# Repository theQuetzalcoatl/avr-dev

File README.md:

# avr-dev

A self made and designed embedded development board with several peripherals/devices to use. On top of that is an embedded kernel with several device drivers, forming an OS.</br>
The project aims to develop a suitable SW architecture and a corresponding HW development board, which can be the foundation of learning and experimentation.

### [Hardware](https://github.com/theQuetzalcoatl/avr-dev/blob/master/HW/README.md "Hardware"):

* LCD
* DAC
* Buzzer
* LEDs & buttons
* Keypad
* UART (potentially USB)
* Temperature sensing
* Light sensing
* Capacitive touch sensing
* Voltage/angle sensing
* Rotary encoder

### [Software](https://github.com/theQuetzalcoatl/avr-dev/blob/master/SW/Application/README.md "Software"):

* A primitive, embedded OS
* Device drivers for HAL
* Application

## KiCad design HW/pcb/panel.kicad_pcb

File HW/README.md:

# Hardware

This file is intended to keep track and present the more detailed informations about the HW part of the project.
The PCB is currently developed in KiCAD. 
---
### HW elements:
* **DAC**: A first order RC low pass filter with variing duty cycle PWM on its input
* **LCD**: A 2x16 display. Backlight can be switched on/off by SW
* **Buzzer**: MOSFET switched, frequency can be set by SW
* **LEDS & buttons**: 4 leds, two push buttons without external pullup resistors
* **Keypad**: a simple 3 by 4 one</br>
      |1|2|3|</br>
      |4|5|6|</br>
      |7|8|9|</br>
      |*|0|#|</br>
* **UART**: Jumper pins for UART  communication, with a suitable connector USB is possible using the CH340G based USB/UART module
* **Temp sensing**: A PT1000 and a current source is used
* **Light sensing**: An LDR is used alongside a regular pot. meter so treshold can also be set
* **Capacitive touch sensing**: Two buttons are made with using only one GPIO each
* **Voltage/angle sensing**: A regular pot meter will supply the devided Vcc voltage. It can be turned and as such, can be used as an angle sensor
* **Rotary encoder**: Capacitors are placed on the MCU pins to help with debouncing

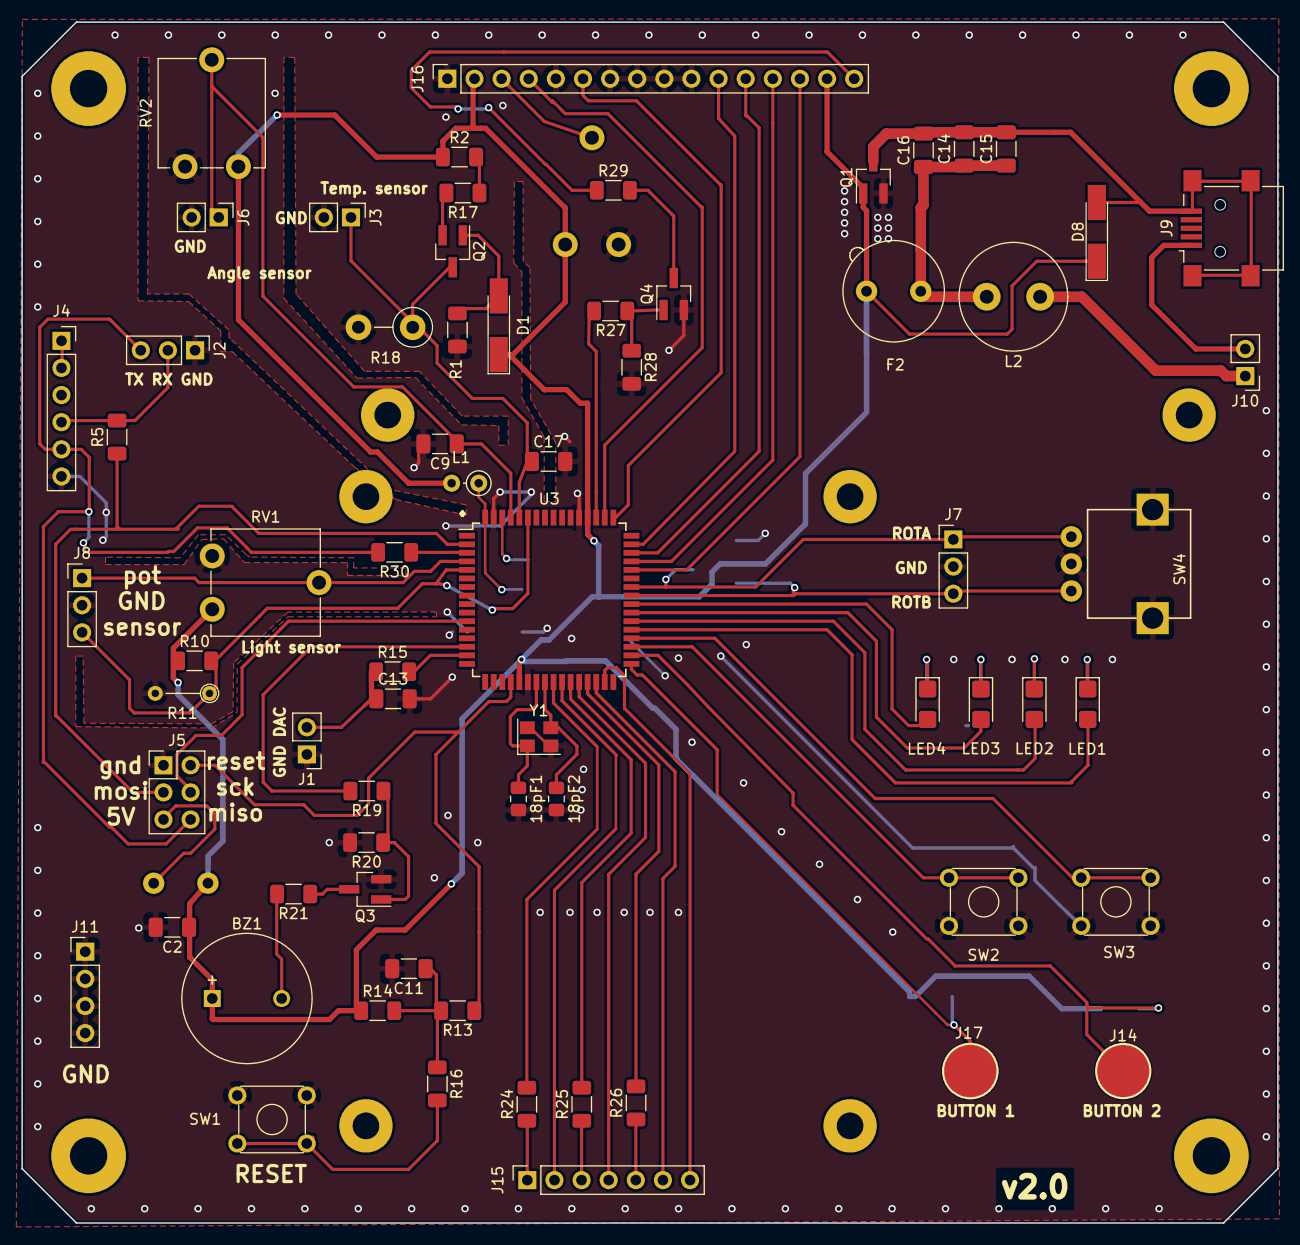
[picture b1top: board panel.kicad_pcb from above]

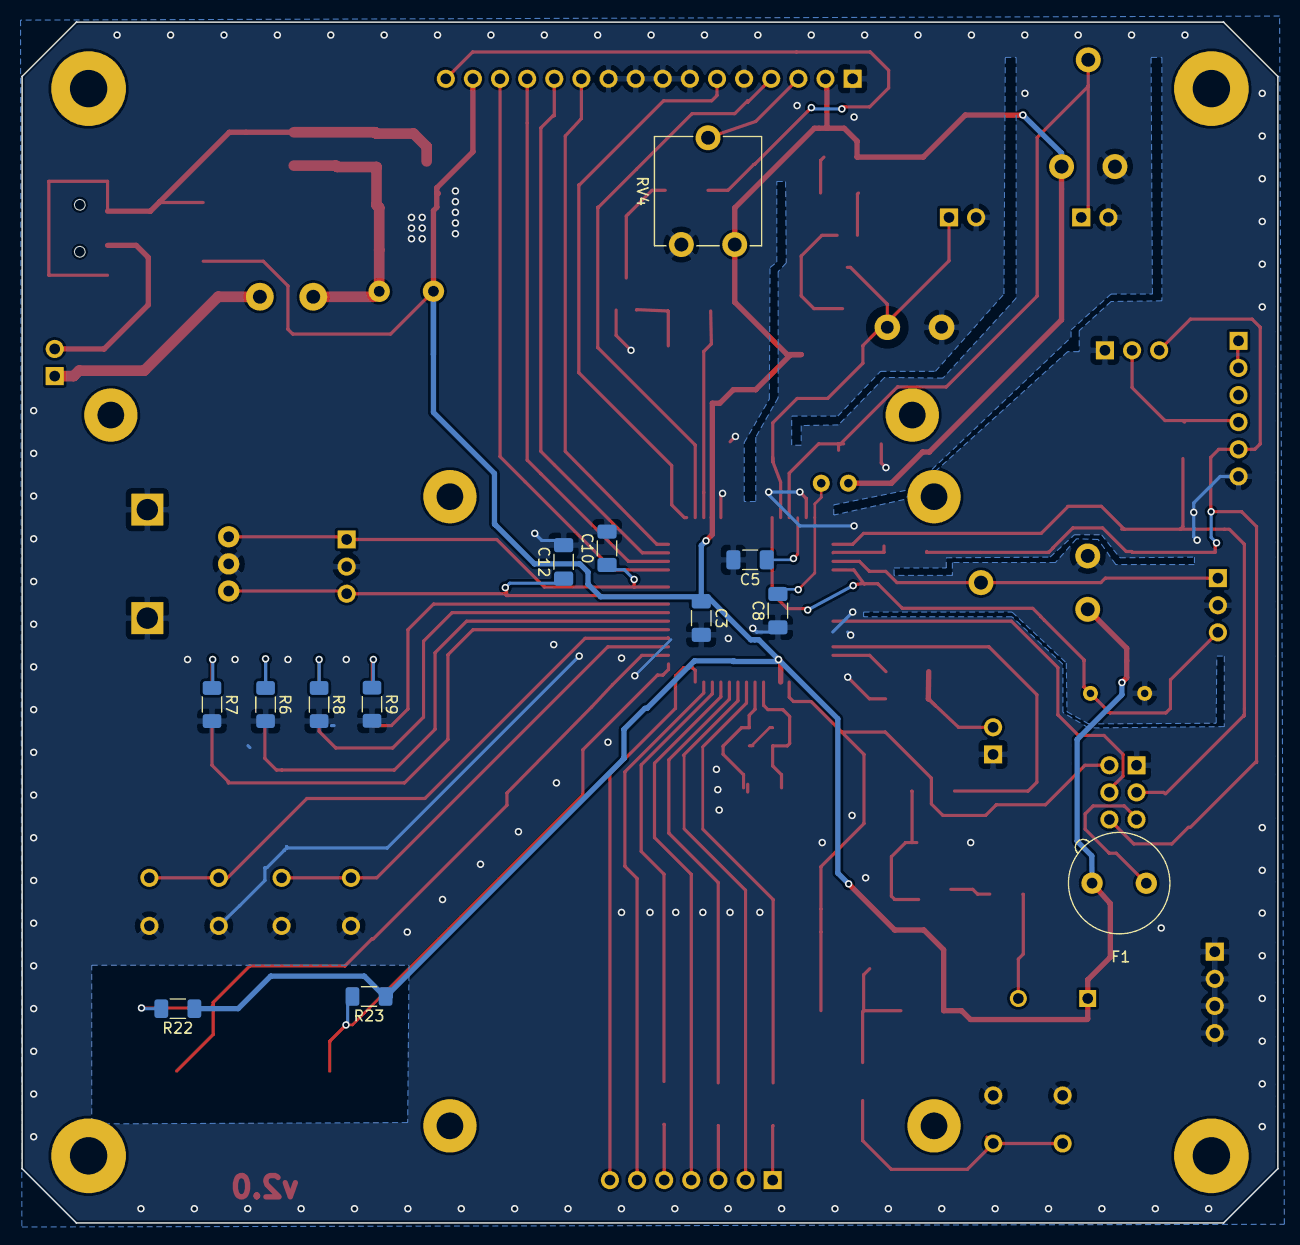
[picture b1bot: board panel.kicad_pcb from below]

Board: 2 copper layers, 117.6 x 112.5 mm, 91 parts (13 on the bottom side), 68 nets.

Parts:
18pF1, 18pF2: 18pF; C_0805_2012Metric_Pad1.18x1.45mm_HandSolder
BZ1: Buzzer; MagneticBuzzer_ProSignal_ABT-410-RC
C2, C5, C9, C16: 100nF; C_1206_3216Metric_Pad1.33x1.80mm_HandSolder
C3: C; C_1206_3216Metric_Pad1.33x1.80mm_HandSolder
C8: 100n; C_1206_3216Metric_Pad1.33x1.80mm_HandSolder
C10, C11, C12, C15, C17: 10nF; C_1206_3216Metric_Pad1.33x1.80mm_HandSolder
C13: 150nF; C_1206_3216Metric_Pad1.33x1.80mm_HandSolder
C14: 1nF; C_1206_3216Metric_Pad1.33x1.80mm_HandSolder
D1: 3_6BreakDown; D_MiniMELF_Handsoldering
D8: 5VBreakdown_Zener; D_MiniMELF_Handsoldering
F1, F2: Fuse_Small; Fuseholder_Fuse_TR5_Littlefuse-No560_No460
J1, J6: Conn_01x02_Male; PinHeader_1x02_P2.54mm_Vertical
J2: USART test points; PinHeader_1x03_P2.54mm_Vertical
J3: Conn_01x02_Male; Pin_Header_Straight_1x02_Pitch2.54mm
J4: uart_conn; PinSocket_1x06_P2.54mm_Vertical
J5: Conn_02x03_Odd_Even; PinHeader_2x03_P2.54mm_Vertical
J7, J8: Conn_01x03_Male; PinHeader_1x03_P2.54mm_Vertical
J9: USB_B_Mini; USB_Mini-B_Lumberg_2486_01_Horizontal
J10: current sense; PinHeader_1x02_P2.54mm_Vertical
J11: GND conn; PinHeader_1x04_P2.54mm_Vertical
J14, J17: TEST_1P; Measurement_Point_Round-SMD-Pad_Big
J15: Conn_01x07_Female; PinSocket_1x07_P2.54mm_Vertical
J16: Conn_01x16; PinSocket_1x16_P2.54mm_Vertical
J19, J23, J28, J29, J30, J31: Conn_01x01; MountingHole_2.5mm_Pad
J24, J25, J26, J27: Conn_01x01; MountingHole_3.5mm_Pad
L1: Ferrite_Bead; L_Axial_L5.3mm_D2.2mm_P2.54mm_Vertical_Vishay_IM-1
L2: L_Core_Ferrite; L_Radial_D10.0mm_P5.00mm_Fastron_07M
LED1, LED2, LED3, LED4: blue; LED_1206_3216Metric_Castellated
Q1, Q3, Q4: Q_NMOS_GSD; SOT-23_Handsoldering
Q2: BC807; SOT-23_Handsoldering
R1, R6, R7, R8, R9: 270; R_1206_3216Metric_Pad1.30x1.75mm_HandSolder
R2: 200; R_1206_3216Metric_Pad1.30x1.75mm_HandSolder
R5, R19, R21, R30: 12; R_1206_3216Metric_Pad1.30x1.75mm_HandSolder
R10: 200k; R_1206_3216Metric_Pad1.30x1.75mm_HandSolder
R11: LDR; R_Axial_DIN0204_L3.6mm_D1.6mm_P5.08mm_Vertical
R13: 470; R_1206_3216Metric_Pad1.30x1.75mm_HandSolder
R14, R15: 10k; R_1206_3216Metric_Pad1.30x1.75mm_HandSolder
R16, R27: 100; R_1206_3216Metric_Pad1.30x1.75mm_HandSolder
R17: 2k7; R_1206_3216Metric_Pad1.30x1.75mm_HandSolder
R18: PT1000; R_Axial_DIN0411_L9.9mm_D3.6mm_P5.08mm_Vertical
R20, R28: 100k; R_1206_3216Metric_Pad1.30x1.75mm_HandSolder
R22, R23: 470k; R_1206_3216Metric_Pad1.30x1.75mm_HandSolder
R24, R25, R26: 2.2k; R_1206_3216Metric_Pad1.30x1.75mm_HandSolder
R29: 91; R_1206_3216Metric_Pad1.30x1.75mm_HandSolder
RV1, RV2, RV4: 10k; Potentiometer_ACP_CA9-V10_Vertical
SW1, SW2, SW3: SW_Push_Dual_OWN; SW_TH_Tactile_Omron_B3F-10xx
SW4: Rotary_Encoder_With_CaseHolder; Rotary_Encoder_CaseHolder
U3: ATMEGA128-16AU; TQFP-64_14x14mm_P0.8mm
Y1: Crystal_GND24_Small; Crystal_SMD_3225-4Pin_3.2x2.5mm

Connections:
+5V: BZ1.1, C2.1, C3.1, D1.1, D8.1, F1.2, F2.2, J16.2, J16.15, L1.2, Q1.1, R2.1, R10.1, R14.1, R22.1, R23.1, RV1.1, RV2.1, RV4.1, U3.21, U3.52
/Input_filter/DC_1: J9.1, J10.2
/Input_filter/DC_2: C14.2, C15.2, C16.2, D8.2, J9.5, J9.6, Q1.3
/Keypad/col_1: R25.2, U3.27
/Keypad/col_2: R24.2, U3.25
/Keypad/col_3: R26.2, U3.29
/Keypad/row_1: J15.2, U3.26
/Keypad/row_2: J15.7, U3.31
/Keypad/row_3: J15.6, U3.30
/Keypad/row_4: J15.4, U3.28
/LCD_/Backlight: R27.2, U3.51
/LCD_/D4: J16.11, U3.47
/LCD_/D5: J16.12, U3.46
/LCD_/D6: J16.13, U3.45
/LCD_/D7: J16.14, U3.44
/LCD_/EN: J16.6, U3.49
/LCD_/RS: J16.4, U3.50
BUTT1: SW2.1, SW2.2, U3.35
BUTT2: SW3.1, SW3.2, U3.36
Buzzer: R19.2, U3.14
Capacitive_button_1: J17.1, R23.2, U3.33
Capacitive_button_2: J14.1, R22.2, U3.34
DAC: R15.2, U3.15
GNDREF: 18pF1.2, 18pF2.2, C2.2, C3.2, C5.2, C8.1, C9.2, C10.2, C11.2, C12.2, C13.2, C17.2, J1.1, J2.1, J3.2, J4.6, J5.1, J6.2, J7.2, J8.2, J11.1, J11.2, J11.3, J11.4, J16.1, J16.5, J16.7, J16.8, J16.9, J16.10, Q1.2, Q3.2, Q4.2, R1.2, R6.2, R7.2, R8.2, R9.2, R11.2, R18.2, R20.2, R28.2, RV1.3, RV2.3, RV4.3, SW1.1, SW1.2, SW2.3, SW2.4, SW3.3, SW3.4, SW4.2, SW4.4, SW4.5, U3.22, U3.53, U3.63, Y1.2, Y1.4
LDR_divider: J8.3, R10.2, R11.1, U3.5, U3.59
LED1: LED1.2, U3.37
LED2: LED2.2, U3.38
LED3: LED3.2, U3.39
LED4: LED4.2, U3.40
MISO: J2.3, J4.5, J5.6, R30.2
MOSI: J5.3, R5.1, U3.2
unnamed: 18pF1.1, U3.23, Y1.1
unnamed: 18pF2.1, U3.24, Y1.3
unnamed: BZ1.2, R21.2
unnamed: C5.1, U3.62
unnamed: C8.2, L1.1, U3.64
unnamed: C11.1, R13.2, R14.2, R16.1
unnamed: C13.1, J1.2, R15.1
unnamed: C14.1, C15.1, C16.1, F2.1, L2.2
unnamed: D1.2, Q2.1, R1.1
unnamed: F1.1, J5.5
unnamed: J2.2, J4.4, R5.2
unnamed: J4.1, J4.2
unnamed: J10.1, L2.1
unnamed: J15.1, R24.1
unnamed: J15.3, R25.1
unnamed: J15.5, R26.1
unnamed: J16.3, RV4.2
unnamed: J16.16, R29.1
unnamed: LED1.1, R7.1
unnamed: LED2.1, R6.1
unnamed: LED3.1, R8.1
unnamed: LED4.1, R9.1
unnamed: Q2.2, R17.2
unnamed: Q3.1, R19.1, R20.1
unnamed: Q3.3, R21.1
unnamed: Q4.1, R27.1, R28.1
unnamed: Q4.3, R29.2
unnamed: R16.2, SW1.3, SW1.4
unnamed: R2.2, R17.1
unnamed: R30.1, U3.3
Pot.meter: J8.1, RV1.2, U3.4
RESET_MEGA: J5.2, R13.1, U3.20
ROTA: C10.1, J7.1, SW4.1, U3.42
ROTB: C12.1, J7.3, SW4.3, U3.41
SCK: J5.4, U3.11
Temperature: C17.1, J3.1, Q2.3, R18.1, U3.60
Voltage_sensor: C9.1, J6.1, RV2.2, U3.61

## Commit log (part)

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2020-03-21 Created and added some content to GITIGNORE.
2020-04-25 Created main Makefile and defined the basic structure of it.
2020-04-26 - Added source code discovering section - Added 'upload' target that will be able to being run
2020-04-26 - Made 'upload' target in main Makefile a phony - Updated Component folder structure to include 'model' folder - Created HSI.h header file which will contain important information about the HW.
2020-04-26 - Created folder structure of OS component, also created several source files
2020-05-02 Updated README.
2020-05-02 - Added HW/readme with some content - Updated System readme, corrected ADC->DAC - Updated some comments is SW Makefile - Added SW readme with some content
2020-05-06 HSI update - Supply voltage - IO treshold values
2020-05-06 Added macros to math.h
2020-05-16 Made TODO list look a little bit nicer
2020-09-04 More points added after examining the v1.0 board
2020-09-28 Updated HW TODOs for V2.0
2020-09-28 - Moved the main Application's content into a new folder - created 'examples' section with, well..examples.
2020-10-04 Corrected PORTB to LCD_PORT during the initialization.
2020-10-07 * Created new, rotary encoder example source code * Modified the license statements at the end of some files
2020-10-29 * corrected GPL in some files * created new example code for the light sensor
2020-11-29 Created new example code for the potmeter ADC.
2020-12-21 New example for the keyboard.
2020-12-24 Created example fir capacitive touch buttons.
2021-01-04 * Removed Makefile because it was unnecessary. Added a bash script in its stead. * Updated README
2021-01-04 Added the gerber files.
2021-05-25 * pictures weren't really changed
2021-05-25 * License and gitignore weren't changed.
2021-05-25 * files were deleted because of folder structure change
2021-05-25 * Renamed for a clearer purpose.
2021-05-25 * updated the examples to fit to the board 2.0v. * added temperature sensing example. * added fuse bit setting for 16 MHz external asc. and ATmega103 compatibility mode disabling
2021-05-30 * The picture was cropped due to image size limitations. Collage is out, trying to upload them individually.
2021-05-30 * Even lower res was created.
2021-05-30 * For some reason, Github differentiated between the same sized pictures, so the full ones were further reduced to 800 width.
2021-07-28 Added bullet points to TODO list for version 3 of the board.
2021-07-28 moved schematic pdf under schematic/
2021-07-28 I don't know exactly what has changed.
2021-07-29 Some of the device drivers were partially implemented
2021-07-29 Created a preemtive kernel with Round Robin scheduling algorithm
2021-07-30 Created a build script. * deletes all object files * compiles all source files * info about size * with an "upload" argument it burns the code to the target
2021-07-30 * Removed current thread pointer - was not being used * removed 'id' from Thread struct, because it was not needed anywhere in the kernel
2021-07-30 Corrected some comments.
2021-07-31 Replaced C stack pointer storing instruction with less, faster assembly instructions. Now context switching is faster.
2021-08-03 * Moved macros from kernel header to c file because currently they are only used in that module * Started adding guide comments to kernel APIs * By reseting TIMER0 at the end of every context restora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
2021-08-05 * decapitalized the drivers folder
2021-08-05 * Changed including of drivers to be lowercase
2021-08-06 * Changed a thread's address' type from snake case to camel case to be consistent with the other ones. * Decremented the minimum stack requirement because it still included RAMPZ register.
2021-08-06 * separated kernel error handling from the main code * kernel error code now prepended by a K * all future error handling shall take place in the error handling files
    * Corrected some error codes
    * Introduced new variable to TCB - num of active threads.
    * is reduced when a thread is halted.
    * will be used when a proper delaying mechanism will be implemented.
    * system now gently halts when the last one of the threads is being deleted.
    * implemented thread number checking
2021-08-09 * Applied cast to operation in order to reduce generated assembly instruction by 2. (Not much, ut it's honest work)
2021-08-09 * Added functionality get a button press. * Created button codes.
2021-08-09 * Moved ATOMIC operation to kernel header in order for the drivers to use. * Did not put 'extern void disable_systick(void)' into kernel header because it should only be reachable by the kernel and i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
2021-08-09 * Created lcd driver with basic functionalities.
2021-08-10 * Removed waiting ticks field form Thread struct because it has no use yet.
2021-08-11 * Got system tick init closer to start of the function because if we shouldn't initialize the drivers if we could not init the systick * Fixed returning error code from init_system_ticking, as it is 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
2021-08-11 * char get_pressed_key --> keypad_get_pressed_key to be clear that that it is the keypad driver's API
2021-08-12 * Changed the kernel to use Timer 2 to generate the systick instead of Timer 0 because the Buzzer will use Timer 0 to generate sound. * Also changed the scaling of the systick based in microseconds i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
2021-08-15 * Properly made init function of the buzzer, which is mostly its timer's initialization * Added device functionalities * buzzing at a certain (unaccurate) frequency * safely stopping the buzzer
2021-08-18 * Modified build script so that it does not burn the uC when compilation fails.
2021-08-19 * Wrote notifying comments about the placement of fields in Thread and TCB data structures. * Corrected max MS tick's justification comment, prescaler was still the old value. * Made the task switch 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
2021-08-19 * Introduced restrictions on the microcontroller frequency. For now, only 8 and 16MHz is allowed. * Introduced minimum systick , and it shall be 100 us. Because now a context switch is about 15 us. *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
2021-08-20 * Some of the configuration macros got CONFIG_ prefix to emphasize that they are changeable configurations
2021-08-23 * Added MindMap file to be ignored.
2021-08-24 * modified, added some comments for better understanding * Added const qualifiers where they were needed * Rearranged the function in kernel.c and created a SYSCALL section for more logical understan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
2021-08-24 * thread state definitions were moved to header, so the application code can use it when getting another thread's state * 'turn_led_on' and 'turn_led_off' functions got atomic write because of a bug 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
2021-08-28 * Added GPLv2 license to all the source files
2021-08-29 * Introduced the first script * it does as the name implies * tested it on the system, cought the first problem, so error_handling was renamed wo kernel_error_handling. * if I changed the header guar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
2021-08-29 * header guard script now have start-end section for better readability in the log stream. Also if it finds at least one wrong header file, it will exit with 1, enabling the build system to halt if n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
2021-09-09 * Introduced kernel version for the application/driver layer which will be the latest tag number.
2021-09-23 * changed the types from capital initiale to <type>_t because i think it is better this way.
2021-09-24 * moved a function, added some explanation to a syscall
2021-09-25 * started reforming the error handling system * introduced error type * maximum of 128 errors can be recognised by the kernel, with the MSB set to 1 * implemented stack registering checking. Now the 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
2021-10-12 * Changed driver system * Short: Now new function pair will be implemented(lease, release) which are analogous to 'open' and 'close'. The caller gets a device ID, and with it, can call certain functi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
2021-10-12 * Updated main and utils to reflect the changes made to the driver system
2021-10-16 * Introduced (re)leasing driver system to LCD. * applied atomic areas when leasing to make it safer, less concurrent. * created LCD driver ID in kernel
2021-10-16 * Added LCD driver ID
2021-10-16 * Updated the user application according to the changes
2021-10-19 * removed lease - release pair, as it is handled by the kernel. * now in critical functions, checking for ownership of the device * implemented internal command sending to simplfiy the initialization.
2021-10-19 * Uptaed example application code
2021-10-22 * Created a new lcd function 'lcd_print' to print strings. * created an internalwrite as well to be faster. * Also found a bug, at startup, if the first thread is run, and runs to exit before a conte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
2021-10-22 * Updated example application.
2021-10-23 * Made it so now if a thread does not release a device before it exits, the kernel we do so on its behalf. * Updated application example
2021-10-30 * registered UART amongs the devices in the kernel
2021-10-30 * Updated example application according to changes made
2021-10-31 * separated the OS code from the Application. * OS is now archived * error checking is applied at each compilation step, resulting in a prevention of uploading to uC
2021-11-13 * Added skeleton + files for encoder device
2021-11-13 * Integrated Buzzer device into the kernel from driver side
2021-12-08 * Changed the syscalls.
2021-12-08 * Updated application
2021-12-12 * New driver functionality by the kernel * devices are initialization can go thourh the kernel, which helps ensuring that no device will be used withouth it being initialized. * 'init_device_drivers'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
2021-12-12 * Updated application.
2021-12-12 * Increased OS version number.
2021-12-20 * Gave the build shell script a more familiar look by introducing the main function. Moreover, it now allows some variables to have proper scope.
2021-12-30 * removed maximum stack size from kernel configuration because right now i dont see any use of it * now every config will have a prefix 'CONFIG_'
2021-12-30 * Increased kernel version number.
2022-01-15 * Introduced ADC driver to the kernel
2022-01-15 * updated test application
2022-01-25 * Updated test test_application
2022-02-10 * Added new system call, 'halt_system', which does just that.
2022-02-10 * Updated test_application
2022-02-11 * Implemented new systemcall. Rebooting the system. * Added a new config because the reset vector is not guaranteed to be at address 0x00
2022-02-25 * Udated test application
2022-03-19 * Corrected 'sound' driver inclusion path
2022-04-13 Committing temporary PCB changes
2022-04-13 minor changes
2022-04-30 * Changed return type of 'acquire_amplifier_offset' function because offset is saved az a static var, referenced inside the function as a pointer
2022-04-30 * moved all the static function declarations to the top
2022-05-26 * introduced the possibility of running the kernel on other timer(s) than T2. For now only T0 is supported additionally. * + a bunch of file ID changes i guess, cause I switched to Ubuntu
2022-05-29 * implemented the showcase application, tetris song is still missing * menu system done * menu sound on/off done * system infos done * music - imperial march done
2022-05-29 * Added 'Tetris' song under 'Music' menu
2022-05-31 * changed hungarian names to english ones.
2022-07-24 * Added GTA SA theme to the songs
2022-07-28 * A new feature is not a major change because it does not modify the users usage of the system
2022-08-13 * Implemented logging functionality. It is a circular fifo which always shows the freshest information. * the kernel config file was expanded accordingly
2022-08-14 * Found and solved infinite loop bug.
2022-10-15 * Implemented uptime in kernel * expanded test application to include uptime functionality * implemented keypad non blocking function * uptime funciotnality can be found in System info/Uptime
2022-10-22 * Made LCD backlight turn off after some time of idleness. * new thread * separated LCD and LCD_BACKLIGHT drivers. * Made new menu 'Games' for the future.
2022-11-04 * Got rid of all the warnings
2022-12-13 * Changed the folder names not to interfere with bash scripts * Started creating new 'Application' section of the prtoject where independent threads can reside in their own environment
2022-12-13 * Got rid of utils.h file, contents were not necessary
2023-02-23 * Moved the songs into Application territory in the folder structure * only have one, common stack * stop functionaliy is removed * intoduced 'load' syscall - hooks a not running thread with the supp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
